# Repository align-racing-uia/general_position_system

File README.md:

<h1 align="center"> General Position System </h1> <br>
<p align="center">
    
</p>

<!-- START doctoc generate TOC please keep comment here to allow auto update -->
<!-- DON'T EDIT THIS SECTION, INSTEAD RE-RUN doctoc TO UPDATE -->
## Table of contents

- [Introduction](#introduction)
- [Align Racing UiA](#alignracinguia)
- [Rules for file structure](#rulesforfilestructure)
- [License](#license)

<!-- END doctoc generated TOC please keep comment here to allow auto update -->

## Introduction

This is the repository for Align Racing's formula student race car's different systems.

## Align Racing UiA

<a href="http://www.alignracing.no/">Align Racing UiA (AR)</a> is a multidisciplinary student organisation at <a href="https://www.uia.no/">The University of Agder (UiA)</a>, that take part in the world’s largest yearly engineering competition; <a href="https://www.imeche.org/events/formula-student">Formula Student (FS)</a>. The organisation continuously consists of around 60 students, from a wide variety of disciplines. The competition includes developing, building, budgeting and marketing a small scale formula type racing car. AR takes this a bit further by having more focus on developing a strong organisation, open for all disciplines, that gives the members a taste of future work-life.

## Rules

## Contribution

## License
All content included in this Git repository is under the license:

Creative Commons Attribution-NonCommercial-ShareAlike 4.0 International

You are free to:
* <b> Share </b> — copy and redistribute the material in any medium or format
* <b> Adapt </b> — remix, transform, and build upon the material

Under the following terms:
* <b> Attribution </b> — You must give appropriate credit, provide a link to the license, and indicate if changes were made. You may do so in any reasonable manner, but not in any way that suggests the licensor endorses you or your use.
* <b> NonCommercial </b> — You may not use the material for commercial purposes.
* <b> ShareAlike </b> — If you remix, transform, or build upon the material, you must distribute your contributions under the same license as the original.
* <b> No additional restrictions </b> — You may not apply legal terms or technological measures that legally restrict others from doing anything the license permits.

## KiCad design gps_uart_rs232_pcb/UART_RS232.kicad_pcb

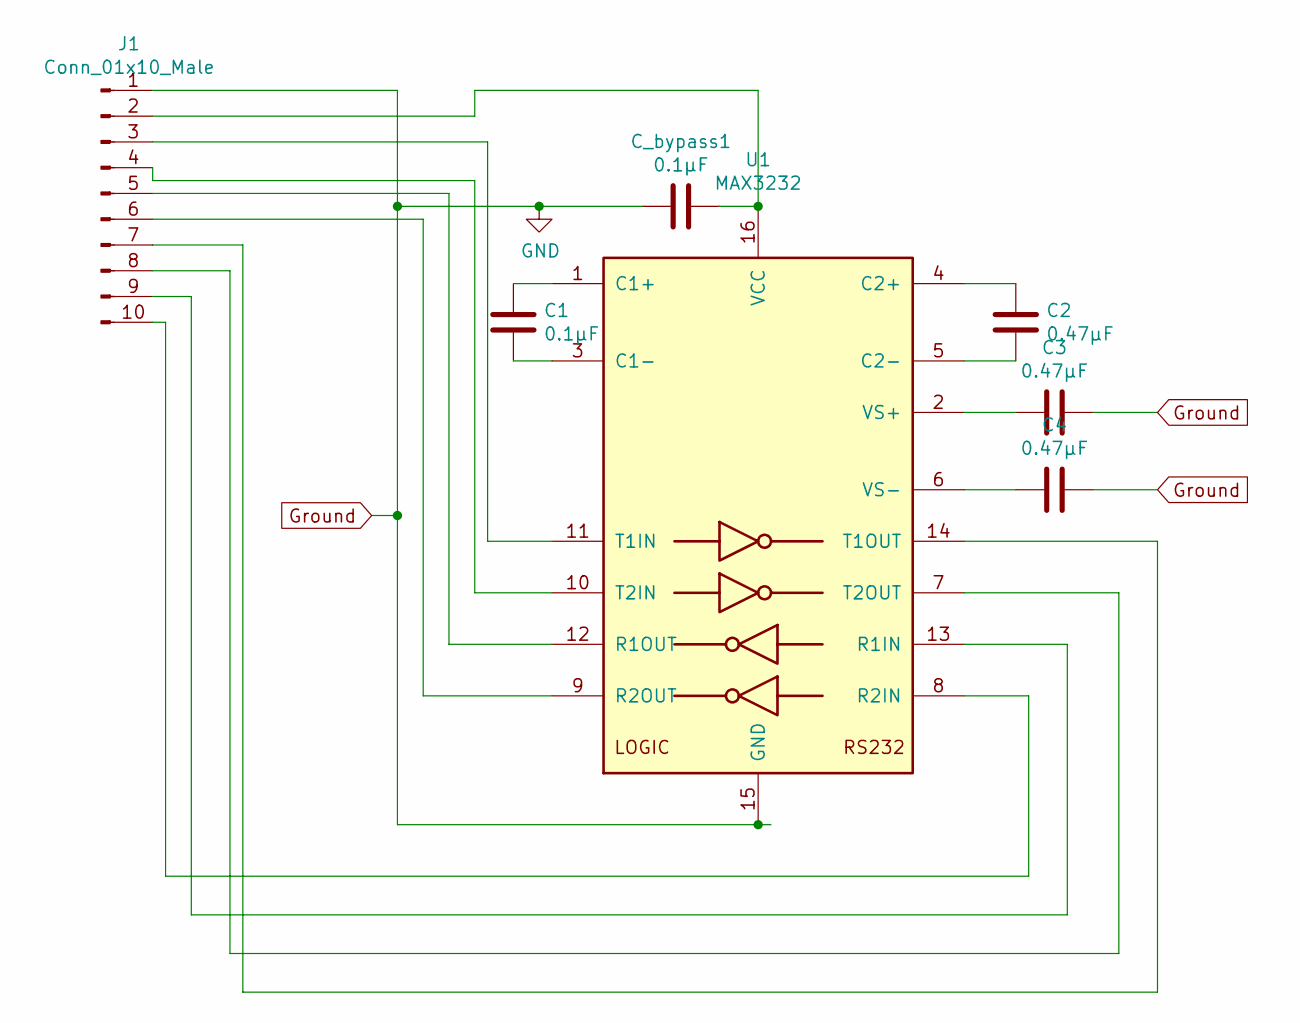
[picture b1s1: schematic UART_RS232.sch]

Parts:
C1: 0.1µF; C_Disc_D8.0mm_W5.0mm_P5.00mm
C2, C3, C4: 0.47µF; C_Disc_D8.0mm_W5.0mm_P5.00mm
C_bypass1: 0.1µF; C_Disc_D8.0mm_W5.0mm_P5.00mm
J1: Conn_01x10_Male; PinHeader_1x10_P2.54mm_Horizontal
U1: MAX3232; DIP-16_W7.62mm

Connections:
Ground: C3.2, C4.2, C_bypass1.1, J1.1, U1.15 (GND)
unnamed: C1.1, U1.1 (C1+)
unnamed: C1.2, U1.3 (C1-)
unnamed: C2.1, U1.4 (C2+)
unnamed: C2.2, U1.5 (C2-)
unnamed: C3.1, U1.2 (VS+)
unnamed: C4.1, U1.6 (VS-)
unnamed: C_bypass1.2, J1.2, U1.16 (VCC)
unnamed: J1.3, U1.11 (T1IN)
unnamed: J1.4, U1.10 (T2IN)
unnamed: J1.5, U1.12 (R1OUT)
unnamed: J1.6, U1.9 (R2OUT)
unnamed: J1.7, U1.14 (T1OUT)
unnamed: J1.8, U1.7 (T2OUT)
unnamed: J1.9, U1.13 (R1IN)
unnamed: J1.10, U1.8 (R2IN)

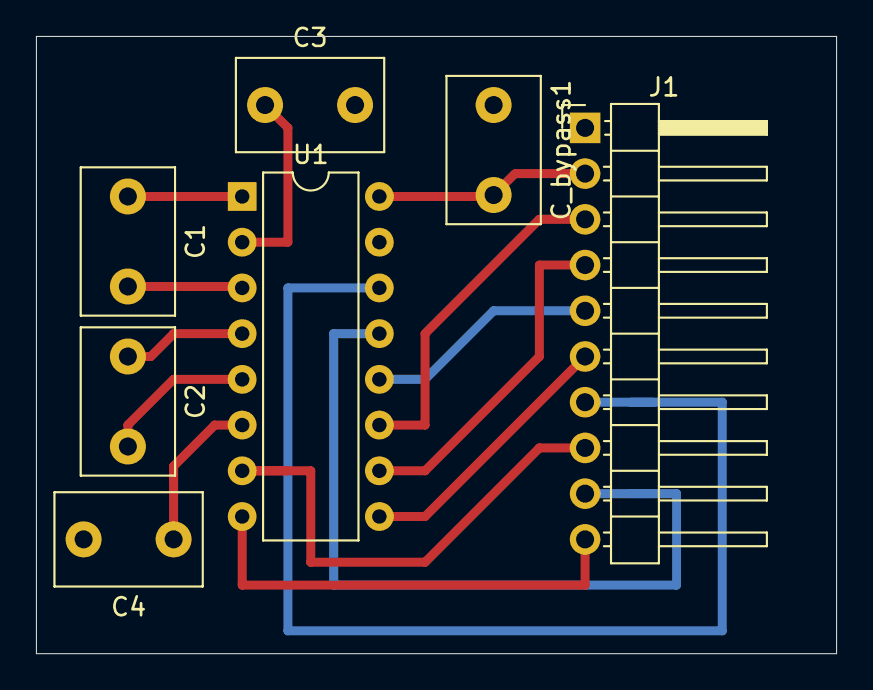
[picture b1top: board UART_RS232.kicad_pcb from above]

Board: 2 copper layers, 44.5 x 34.3 mm, 7 parts (0 on the bottom side), 16 nets.

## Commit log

2021-08-01 Directory refactoring.
